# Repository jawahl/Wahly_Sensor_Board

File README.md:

# Wahly_Sensor_Board

**Hardware Overview**:

This board is designed around the STM32F3 microcontroller, LIS3DHTR accelerometer, and SHT30 temperature & humidity sensor. USB powered, SWD debug/programming, footprint for additional FLASH memory chip (SOIC-8), ADC/TIM pin header breakouts for external peripherals. 

Schematic and layout done in KiCAD, assembly/fab done with JLCPCB.

# Repository Definition:

**Wahly_KiCAD** - Contains all KiCAD project files. Includes schematic (with pdf viewable) and layout files.

**Firmware** - Contains all firmware files for the Wahly Sensor Board. Includes STM32CubeIDE .ioc file with all necessary driver/HAL/main C files.

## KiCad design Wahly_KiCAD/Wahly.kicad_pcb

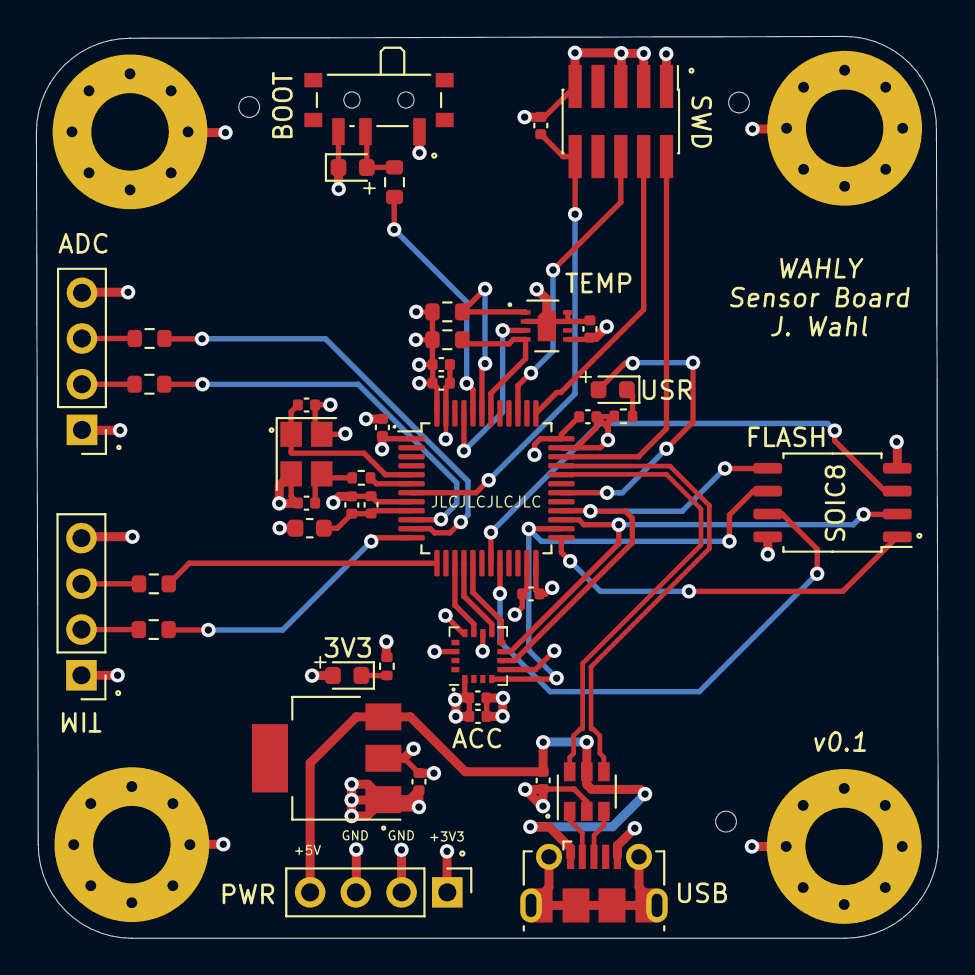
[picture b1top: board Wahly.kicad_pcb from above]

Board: 4 copper layers, 50.1 x 50.1 mm, 46 parts (0 on the bottom side), 40 nets.

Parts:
C1, C2, C5: 10uF; C_0402_1005Metric
C3, C4, C7, C8, C9, C10, C15: 100nF; C_0402_1005Metric
C6: 4,7uF; C_0402_1005Metric
C11: 10nF; C_0402_1005Metric
C12: 1uF; C_0402_1005Metric
C13, C14: 20pF; C_0402_1005Metric
D1: Green; LED_0603_1608Metric
D2, D4: Red; LED_0603_1608Metric
FB1: 600 @ 600MHz; L_0603_1608Metric
H1, H2, H3, H4: MountingHole_Pad; MountingHole_4.3mm_M4_Pad_Via
J1: USB_B_Micro; USB_Micro-B_Molex-105017-0001
J2: Power; PinHeader_1x04_P2.54mm_Vertical
J3: ADC; PinHeader_1x04_P2.54mm_Vertical
J4: SWD; PinHeader_2x05_P1.27mm_Vertical_SMD
J5: TIM2; PinHeader_1x04_P2.54mm_Vertical
R1, R2: 2k2; R_0603_1608Metric
R3: 47; R_0402_1005Metric
R4, R5: 1k; R_0402_1005Metric
R6, R7, R8, R10: 22; R_0603_1608Metric
R9: 10k; R_0603_1608Metric
SW1: SW_SPDT; SW_SPDT_PCM12
U1: LM1117-3.3; SOT-223
U2: USBLC6-2SC6; SOT-23-6
U3: SHT30-DIS; Sensirion_DFN-8-1EP_2.5x2.5mm_P0.5mm_EP1.1x1.7mm
U4: LIS3DHTR; LGA-16_3x3mm_P0.5mm
U5: STM32F302C8Tx; LQFP-48_7x7mm_P0.5mm
U6: W25Q32JVSS; SOIC-8_5.23x5.23mm_P1.27mm
Y1: 16MHz; Crystal_SMD_TXC_7M-4Pin_3.2x2.5mm

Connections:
+3.3VA: C11.1, C12.1, FB1.1, U5.9
+3V3: C2.1, C3.1, C4.1, C5.1, C6.1, C7.1, C8.1, C9.1, C10.1, D1.2, FB1.2, J2.1, J3.1, J4.1, J5.1, R1.1, R2.1, SW1.1, U1.2, U3.5, U4.1, U4.14, U5.1, U5.24, U5.36, U5.48, U6.8
+5V: C1.1, J1.1, J2.4, U1.3, U2.5
ACC_CS: U4.8, U5.17
ACC_INT1: U4.11, U5.15
ACC_INT2: U4.9, U5.16
ADC1_IN1: R6.2, U5.10
ADC1_IN2: R7.2, U5.11
BOOT0: R9.2, U5.44
FLASH_!HOLD: U5.20, U6.7
FLASH_!WP: U5.19, U6.3
GND: C1.2, C2.2, C3.2, C4.2, C5.2, C6.2, C7.2, C8.2, C9.2, C10.2, C11.2, C12.2, C13.2, C14.2, C15.2, D4.1, H1.1, H2.1, H3.1, H4.1, J1.5, J2.2, J2.3, J3.4, J4.3, J4.5, J4.9, J5.4, R4.2, R5.2, SW1.3, U1.1, U2.2, U3.2, U3.7, U3.8, U3.9, U4.5, U4.10, U4.12, U5.8, U5.23, U5.35, U5.47, U6.4, Y1.2, Y1.4
HSE_IN: C13.1, U5.5, Y1.1
HSE_OUT: R3.1, U5.6
I2C1_SCL: R2.2, U3.4, U5.42
I2C1_SDA: R1.2, U3.1, U5.43
NRST: C15.1, J4.10, U5.7
unnamed: C14.1, R3.2, Y1.3
unnamed: D1.1, R4.1
unnamed: D2.1, R5.1
unnamed: D2.2, U5.30
unnamed: D4.2, R9.1, SW1.2
unnamed: J3.2, R6.1
unnamed: J3.3, R7.1
unnamed: J5.2, R8.1
unnamed: J5.3, R10.1
SPI2_!CS: U5.25, U6.1
SPI2_MISO: U4.7, U5.27, U6.2
SPI2_MOSI: U4.6, U5.28, U6.5
SPI2_SCK: U4.4, U5.26, U6.6
SWD_DIO: J4.2, U5.34
SWD_SWCLK: J4.4, U5.37
SWD_SWO: J4.6, U5.39
TEMP_INT: U3.3, U5.45
TIM2_CH3: R8.2, U5.12
TIM2_CH4: R10.2, U5.13
USB_CONN_D+: J1.3, U2.3
USB_CONN_D-: J1.2, U2.1
USB_D+: U2.4, U5.33
USB_D-: U2.6, U5.32

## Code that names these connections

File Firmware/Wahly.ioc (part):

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Mcu.Name=STM32F302C(6-8)Tx
Mcu.Package=LQFP48
Mcu.UserName=STM32F302C8Tx
PA11.Mode=Device
PA11.Signal=USB_DM
PA12.Mode=Device
PA12.Signal=USB_DP
PA13.Mode=Serial_Wire
PA13.Signal=SYS_JTMS-SWDIO
PA14.Mode=Serial_Wire
PA14.Signal=SYS_JTCK-SWCLK
PA15.Mode=I2C
PA15.Signal=I2C1_SCL
PB13.Mode=Full_Duplex_Master
PB13.Signal=SPI2_SCK
PB14.Mode=Full_Duplex_Master
PB14.Signal=SPI2_MISO
PB15.Mode=Full_Duplex_Master
PB15.Signal=SPI2_MOSI
PB7.Mode=I2C
PB7.Signal=I2C1_SDA
PF0-OSC_IN.Mode=HSE-External-Oscillator
PF0-OSC_IN.Signal=RCC_OSC_IN
PF1-OSC_OUT.Mode=HSE-External-Oscillator
PF1-OSC_OUT.Signal=RCC_OSC_OUT
RCC.HSEPLLFreq_Value=8000000
RCC.HSE_VALUE=8000000
RCC.SYSCLKFreq_VALUE=48000000
RCC.SYSCLKSourceVirtual=RCC_SYSCLKSOURCE_PLLCLK
board=custom

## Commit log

2021-10-31 initial upload of files
2021-10-31 save updates
2021-11-03 pdf schematic
2021-11-11 Silkscreen & DRC
